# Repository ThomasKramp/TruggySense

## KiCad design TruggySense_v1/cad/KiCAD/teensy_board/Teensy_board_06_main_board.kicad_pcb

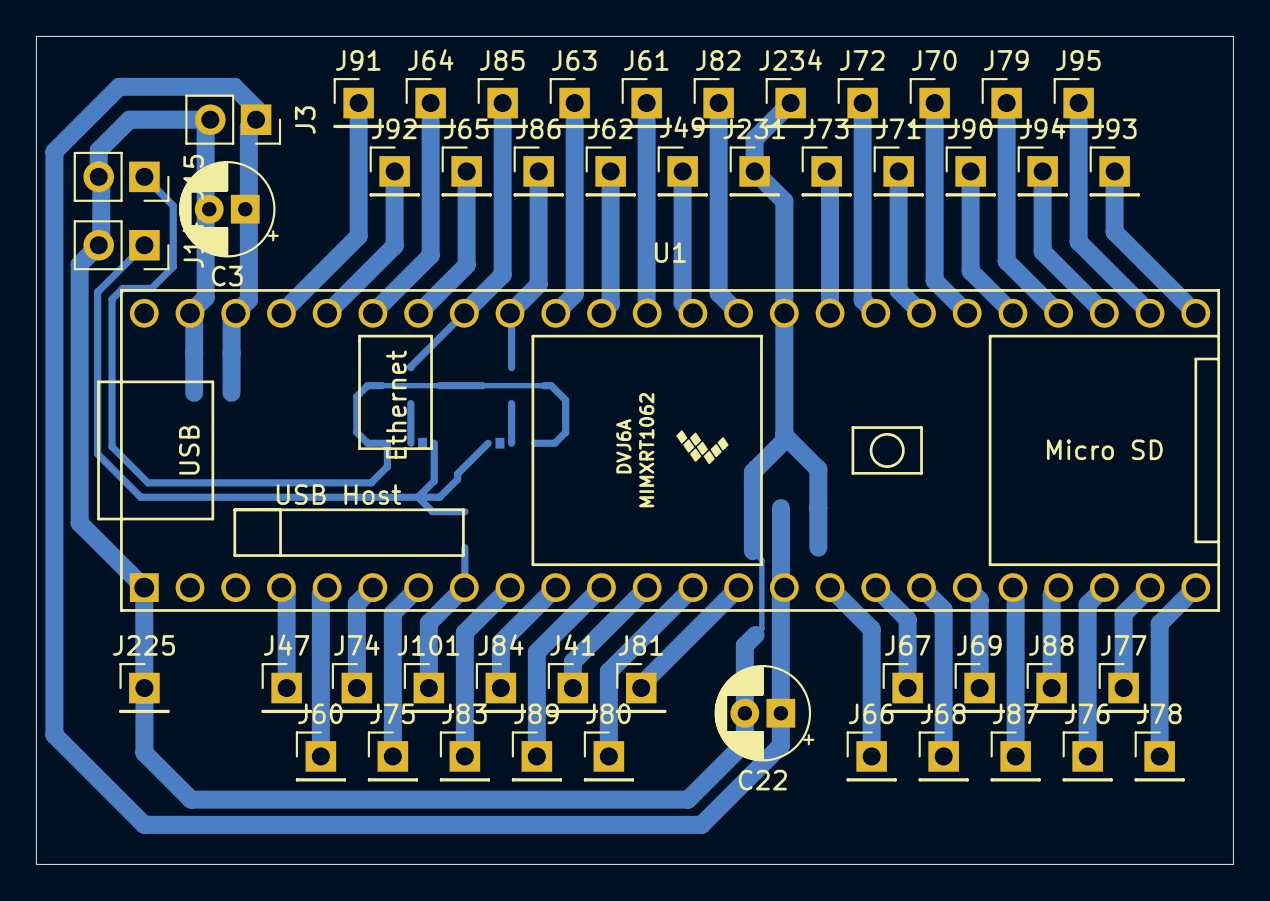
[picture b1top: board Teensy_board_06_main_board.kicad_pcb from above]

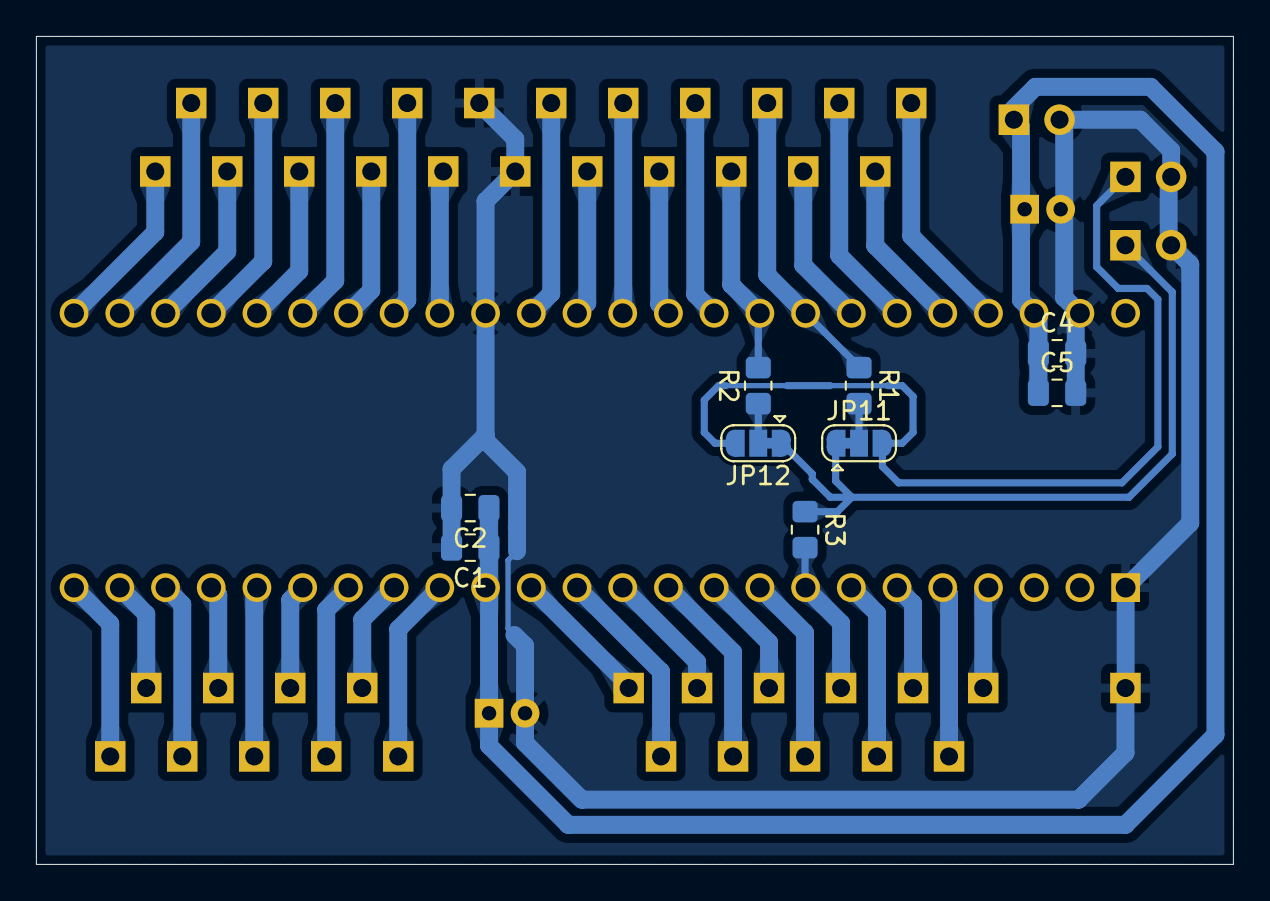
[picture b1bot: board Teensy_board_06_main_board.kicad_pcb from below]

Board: 2 copper layers, 66.5 x 46.0 mm, 58 parts (9 on the bottom side), 46 nets.

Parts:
C1, C4: 10µ; C_0805_2012Metric_Pad1.18x1.45mm_HandSolder
C2, C5: 10n; C_0805_2012Metric_Pad1.18x1.45mm_HandSolder
C3, C22: 100µ; CP_Radial_D5.0mm_P2.00mm
J3, J14, J15: Conn_01x02; PinSocket_1x02_P2.54mm_Vertical
J41, J47, J49, J60, J61, J62, J63, J64, J65, J66, J67, J68, J69, J70, J71, J72, J73, J74, J75, J76, J77, J78, J79, J80, J81, J82, J83, J84, J85, J86, J87, J88, J89, J90, J91, J92, J93, J94, J95, J101, J225, J231, J234: Conn_01x01; PinHeader_1x01_P2.54mm_Vertical
JP11, JP12: SolderJumper_3_Bridged12; SolderJumper-3_P1.3mm_Bridged12_RoundedPad1.0x1.5mm
R1, R2: 4k7; R_0805_2012Metric_Pad1.20x1.40mm_HandSolder
R3: 2k2; R_0805_2012Metric_Pad1.20x1.40mm_HandSolder
U1: Teensy4.1; Teensy41

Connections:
1_Wire: J101.1, R3.2, U1.8 (6_OUT1D)
+3.3V: J14.1, JP11.1 (A), JP12.1 (A), R3.1
+5V: J15.1, JP11.3 (B), JP12.3 (B)
ADC_I_JET: J72.1, U1.32 (40_A16)
ADC_I_M_FL: J68.1, U1.18 (26_A12_MOSI1)
ADC_I_M_FR: J67.1, U1.17 (25_A11_RX6_SDA2)
ADC_I_M_RL: J70.1, U1.30 (38_CS1_IN1)
ADC_I_M_RR: J69.1, U1.19 (27_A13_SCK1)
ADC_I_SERVO: J73.1, U1.33 (41_A17)
ADC_I_TEENSY: J71.1, U1.31 (39_MISO1_OUT1A)
ADC_V_B_C1: J49.1, U1.36 (14_A0_TX3_SPDIF_OUT)
ADC_V_B_C2: J61.1, U1.37 (15_A1_RX3_SPDIF_IN)
ADC_V_B_C3: J62.1, U1.38 (16_A2_RX4_SCL1)
ADC_V_B_C4: J63.1, U1.39 (17_A3_TX4_SDA1)
ADC_V_JET: J66.1, U1.16 (24_A10_TX6_SCL2)
ADC_V_MCU: J65.1, U1.42 (20_A6_TX5_LRCLK1)
ADC_V_PER: J64.1, U1.43 (21_A7_RX5_BCLK1)
EN_M_FL: J78.1, U1.24 (32_OUT1B)
EN_M_FR: J79.1, U1.28 (36_CS)
EN_M_RL: J76.1, U1.22 (30_CRX3)
EN_M_RR: J77.1, U1.23 (31_CTX3)
EN_W_FL: J74.1, U1.6 (4_BCLK2)
EN_W_FR: J75.1, U1.7 (5_IN2)
EN_W_RL: J47.1, U1.4 (2_OUT2)
EN_W_RR: J60.1, U1.5 (3_LRCLK2)
GND: C1.2, C2.2, C3.2, C4.2, C5.2, C22.2, J3.2, J14.2, J15.2, J225.1, J231.1, J234.1, U1.1 (GND), U1.34 (GND), U1.47 (GND)
GPS_RX: J84.1, U1.10 (8_TX2_IN1)
GPS_TX: J83.1, U1.9 (7_RX2_OUT1A)
I2C_SCL: J85.1, R1.1, U1.41 (19_A5_SCL)
I2C_SDA: J86.1, R2.2, U1.40 (18_A4_SDA)
IBUS_RX: J94.1, U1.27 (35_TX8)
IBUS_TX: J95.1, U1.26 (34_RX8)
LED_1: J87.1, U1.20 (28_RX7)
LED_2: J88.1, U1.21 (29_TX7)
unnamed: JP11.2 (C), R1.2
unnamed: JP12.2 (C), R2.1
PWM_ESC_M_FL: J91.1, U1.45 (23_A9_CRX1_MCLK1)
PWM_ESC_M_FR: J90.1, U1.29 (37_CS)
PWM_ESC_M_RL: J89.1, U1.11 (9_OUT1C)
PWM_ESC_M_RR: J92.1, U1.44 (22_A8_CTX1)
PWM_ESC_SERVO: J93.1, U1.25 (33_MCLK2)
SPI_CS: J41.1, U1.12 (10_CS_MQSR)
SPI_MISO: J81.1, U1.14 (12_MISO_MQSL)
SPI_MOSI: J80.1, U1.13 (11_MOSI_CTX1)
SPI_SCK: J82.1, U1.35 (13_SCK_LED)
VCC: C1.1, C2.1, C3.1, C4.1, C5.1, C22.1, J3.1, U1.15 (3V3), U1.46 (3V3)

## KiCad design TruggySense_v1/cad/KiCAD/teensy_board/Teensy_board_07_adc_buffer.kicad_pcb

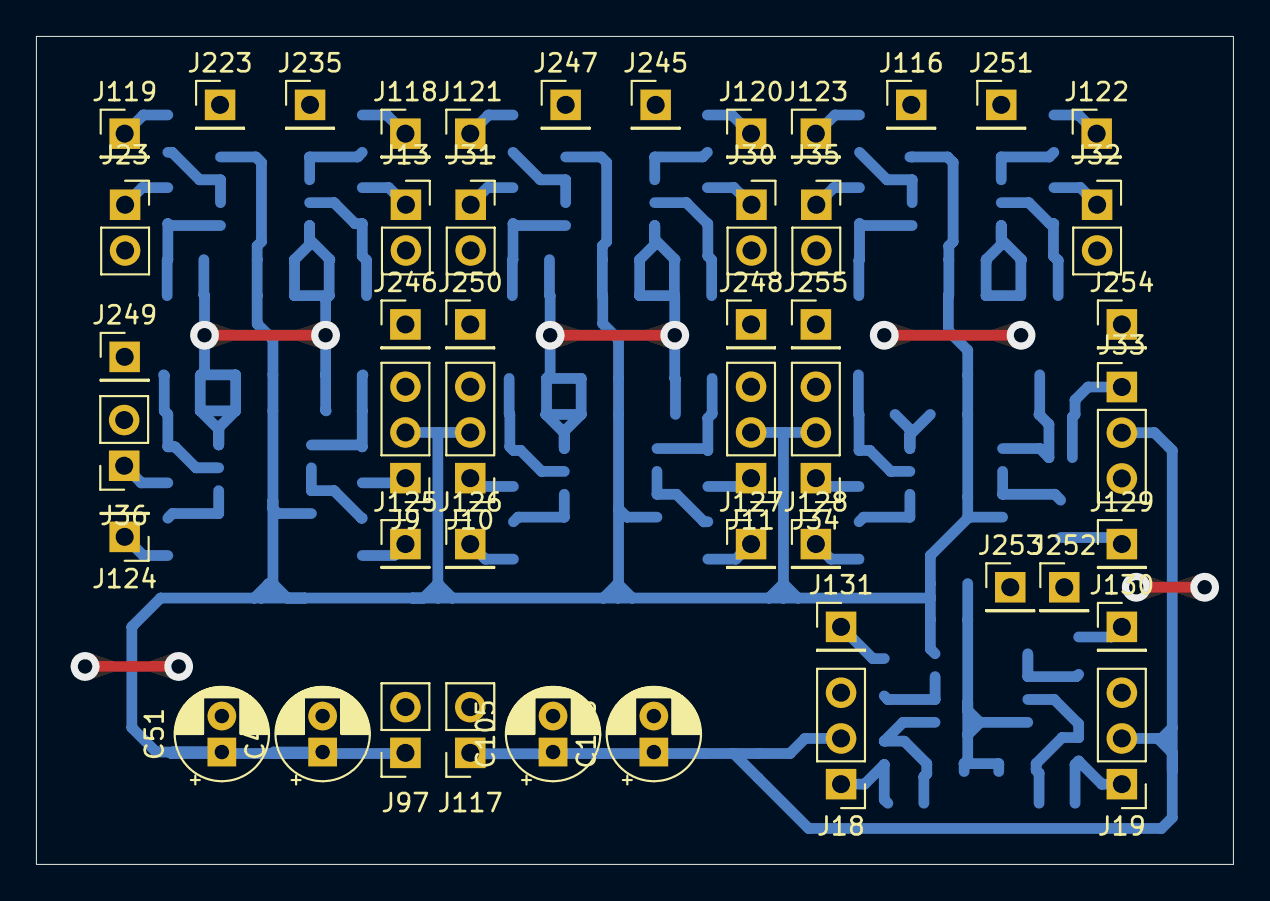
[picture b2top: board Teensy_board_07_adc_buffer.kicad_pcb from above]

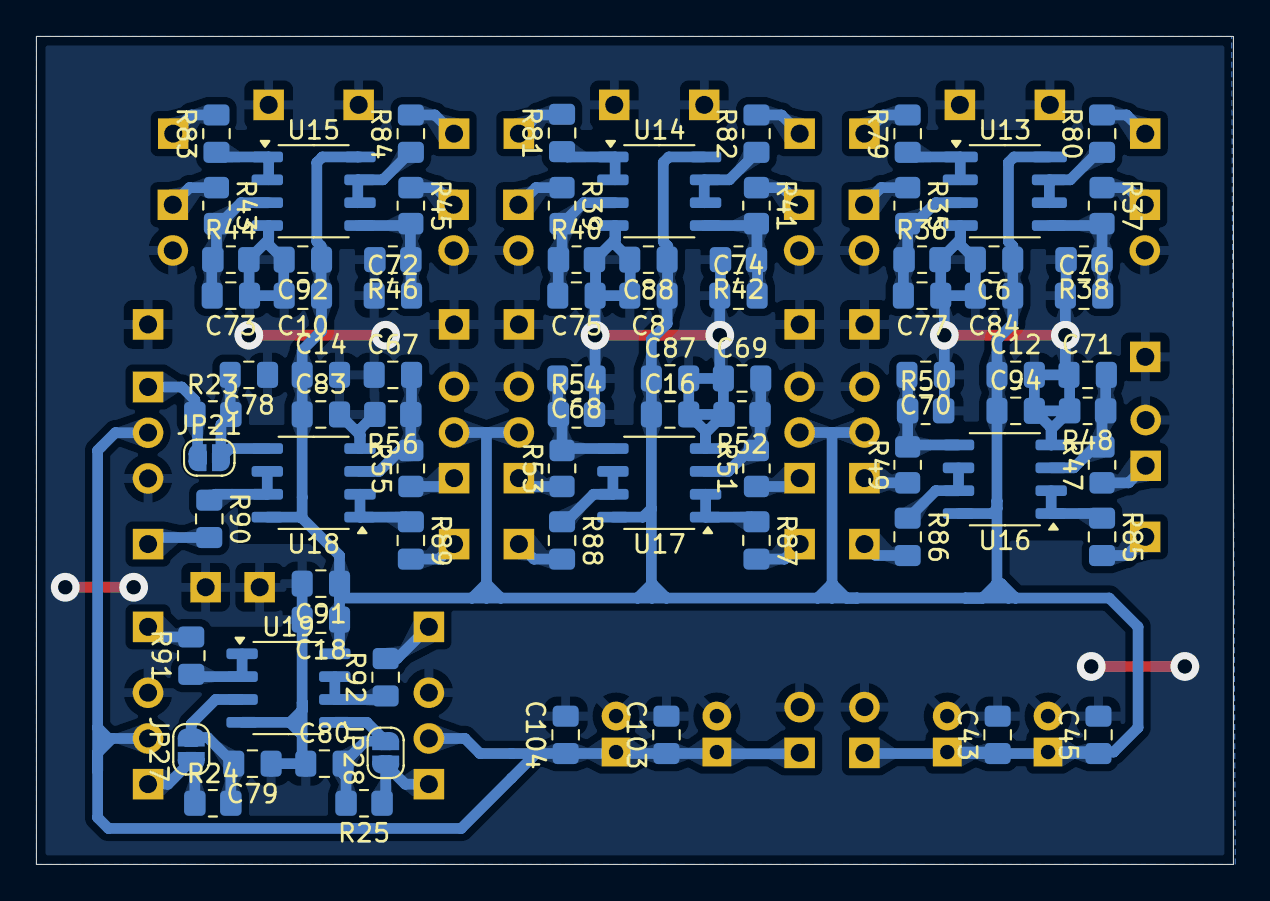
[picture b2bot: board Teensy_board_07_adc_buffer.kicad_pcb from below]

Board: 2 copper layers, 66.5 x 46.0 mm, 129 parts (81 on the bottom side), 24 nets.

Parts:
C6, C8, C10, C12, C14, C16, C18: 10u; C_0805_2012Metric_Pad1.18x1.45mm_HandSolder
C43, C45, C103: 10µ; C_0805_2012Metric_Pad1.18x1.45mm_HandSolder
C49, C51, C105, C106: 100µ; CP_Radial_D5.0mm_P2.00mm
C67, C68, C69, C70, C71, C72, C73, C74, C75, C76, C77, C78, C79, C80: 1µ; C_0805_2012Metric_Pad1.18x1.45mm_HandSolder
C83, C84, C87, C88, C91, C92, C94, C104: 10n; C_0805_2012Metric_Pad1.18x1.45mm_HandSolder
J9: CUR_M_FR; PinHeader_1x03_P2.54mm_Vertical
J10: CUR_M_FL; PinHeader_1x03_P2.54mm_Vertical
J11: CUR_M_RR; PinHeader_1x03_P2.54mm_Vertical
J13: V_BATT_C1; PinSocket_1x02_P2.54mm_Vertical
J18: CUR_SERVO; PinHeader_1x03_P2.54mm_Vertical
J19: CUR_JETSON; PinHeader_1x03_P2.54mm_Vertical
J23: V_BATT_C2; PinSocket_1x02_P2.54mm_Vertical
J30: V_BATT_C3; PinSocket_1x02_P2.54mm_Vertical
J31: V_BATT_C4; PinSocket_1x02_P2.54mm_Vertical
J32: VCC_PER_3V3; PinSocket_1x02_P2.54mm_Vertical
J33: CUR_TEENSY; PinHeader_1x03_P2.54mm_Vertical
J34: CUR_M_RL; PinHeader_1x03_P2.54mm_Vertical
J35: VCC_MCU_3V3; PinSocket_1x02_P2.54mm_Vertical
J36: VCC_JET_5V; PinSocket_1x02_P2.54mm_Vertical
J97, J117: Conn_01x02; PinSocket_1x02_P2.54mm_Vertical
J116, J118, J119, J120, J121, J122, J123, J124, J125, J126, J127, J128, J129, J130, J131, J223, J235, J245, J246, J247, J248, J249, J250, J251, J252, J253, J254, J255: Conn_01x01; PinHeader_1x01_P2.54mm_Vertical
JP21, JP27, JP28: SolderJumper_2_Open; SolderJumper-2_P1.3mm_Open_RoundedPad1.0x1.5mm
R23, R24, R25, R35, R37, R39, R41, R43, R45, R47, R49, R51, R53, R55: 10k; R_0805_2012Metric_Pad1.20x1.40mm_HandSolder
R36, R38, R40, R42: 33k; R_0805_2012Metric_Pad1.20x1.40mm_HandSolder
R44, R46: 82k; R_0805_2012Metric_Pad1.20x1.40mm_HandSolder
R48, R50, R52, R54, R56: 18k; R_0805_2012Metric_Pad1.20x1.40mm_HandSolder
R79, R80, R81, R82, R83, R84, R85, R86, R87, R88, R89, R90, R91, R92: 10; C_0805_2012Metric_Pad1.18x1.45mm_HandSolder
U13: OPA2890ID; SOIC-8_3.9x4.9mm_P1.27mm
U14, U15, U16, U17, U18, U19: OPA2890ID; SO-8_3.9x4.9mm_P1.27mm

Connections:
+3.3V: C103.1, C104.1, C105.1, C106.1, J18.2, J19.2, J33.2, J117.1
+5V: C6.1, C8.1, C10.1, C12.1, C14.1, C16.1, C18.1, C43.1, C45.1, C49.1, C51.1, C83.1, C84.1, C87.1, C88.1, C91.1, C92.1, C94.1, J9.2, J10.2, J11.2, J34.2, J97.1, U13.8 (V+), U14.8 (V+), U15.8 (V+), U16.8 (V+), U17.8 (V+), U18.8 (V+), U19.8 (V+)
/ADC inputs/Buffer/IN_8: C70.2, R49.2, R50.1, U16.5 (+)
/ADC inputs/Buffer/IN_9: C69.2, R51.2, R52.1, U17.3 (+)
/ADC inputs/Buffer/IN_10: C68.2, R53.2, R54.1, U17.5 (+)
/ADC inputs/Buffer/IN_11: C67.2, R55.2, R56.1, U18.3 (+)
/ADC inputs/Buffer/IN_12: C78.2, JP21.2 (B), R23.2, U18.5 (+)
/ADC inputs/Buffer/IN_13: C79.2, JP27.2 (B), R24.2, U19.3 (+)
/ADC inputs/Buffer/IN_14: C80.2, JP28.2 (B), R25.2, U19.5 (+)
/ADC inputs/Buffer/OUT_8: J125.1, R86.2
/ADC inputs/Buffer/OUT_9: J126.1, R87.2
/ADC inputs/Buffer/OUT_10: J127.1, R88.2
/ADC inputs/Buffer/OUT_11: J128.1, R89.2
/ADC inputs/Buffer/OUT_12: J129.1, R90.2
/ADC inputs/Buffer/OUT_13: J130.1, R91.2
/ADC inputs/Buffer/OUT_14: J131.1, R92.2
GND: C6.2, C8.2, C10.2, C12.2, C14.2, C16.2, C18.2, C43.2, C45.2, C49.2, C51.2, C67.1, C68.1, C69.1, C70.1, C71.1, C72.1, C73.1, C74.1, C75.1, C76.1, C77.1, C78.1, C79.1, C80.1, C83.2, C84.2, C87.2, C88.2, C91.2, C92.2, C94.2, C103.2, C104.2, C105.2, C106.2, J9.3, J10.3, J11.3, J13.2, J18.3, J19.3, J23.2, J30.2, J31.2, J32.2, J33.3, J34.3, J35.2, J36.2, J97.2, J116.1, J117.2, J223.1, J235.1, J245.1, J246.1, J247.1, J248.1, J249.1, J250.1, J251.1, J252.1, J253.1, J254.1, J255.1, R36.2, R38.2, R40.2, R42.2, R44.2, R46.2, R48.2, R50.2, R52.2, R54.2, R56.2, U13.4 (V-), U14.4 (V-), U15.4 (V-), U16.4 (V-), U17.4 (V-), U18.4 (V-), U19.4 (V-)
unnamed: J9.1, R49.1
unnamed: J10.1, R51.1
unnamed: J11.1, R53.1
unnamed: J18.1, JP28.1 (A), R25.1
unnamed: J19.1, JP27.1 (A), R24.1
unnamed: J33.1, JP21.1 (A), R23.1
unnamed: J34.1, R55.1

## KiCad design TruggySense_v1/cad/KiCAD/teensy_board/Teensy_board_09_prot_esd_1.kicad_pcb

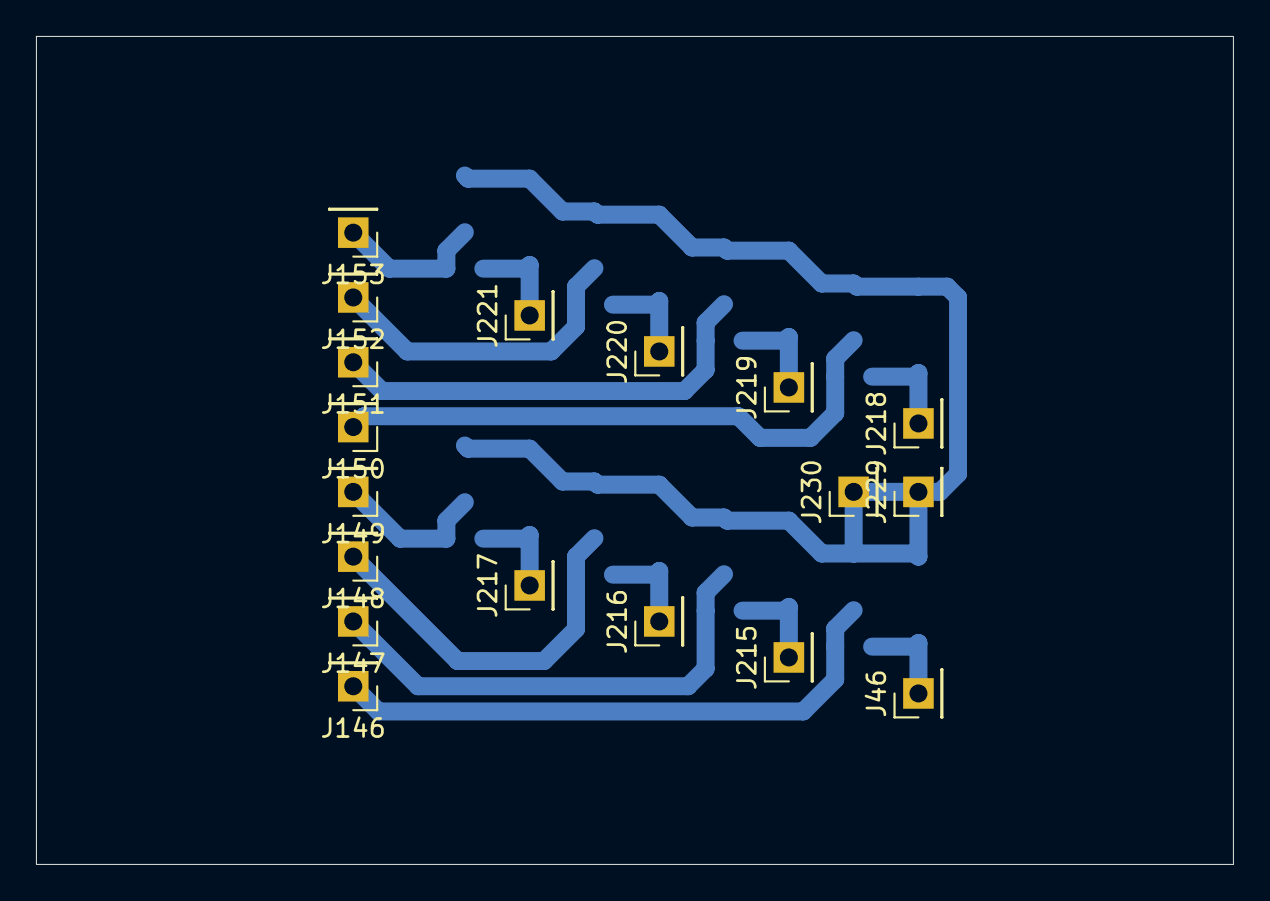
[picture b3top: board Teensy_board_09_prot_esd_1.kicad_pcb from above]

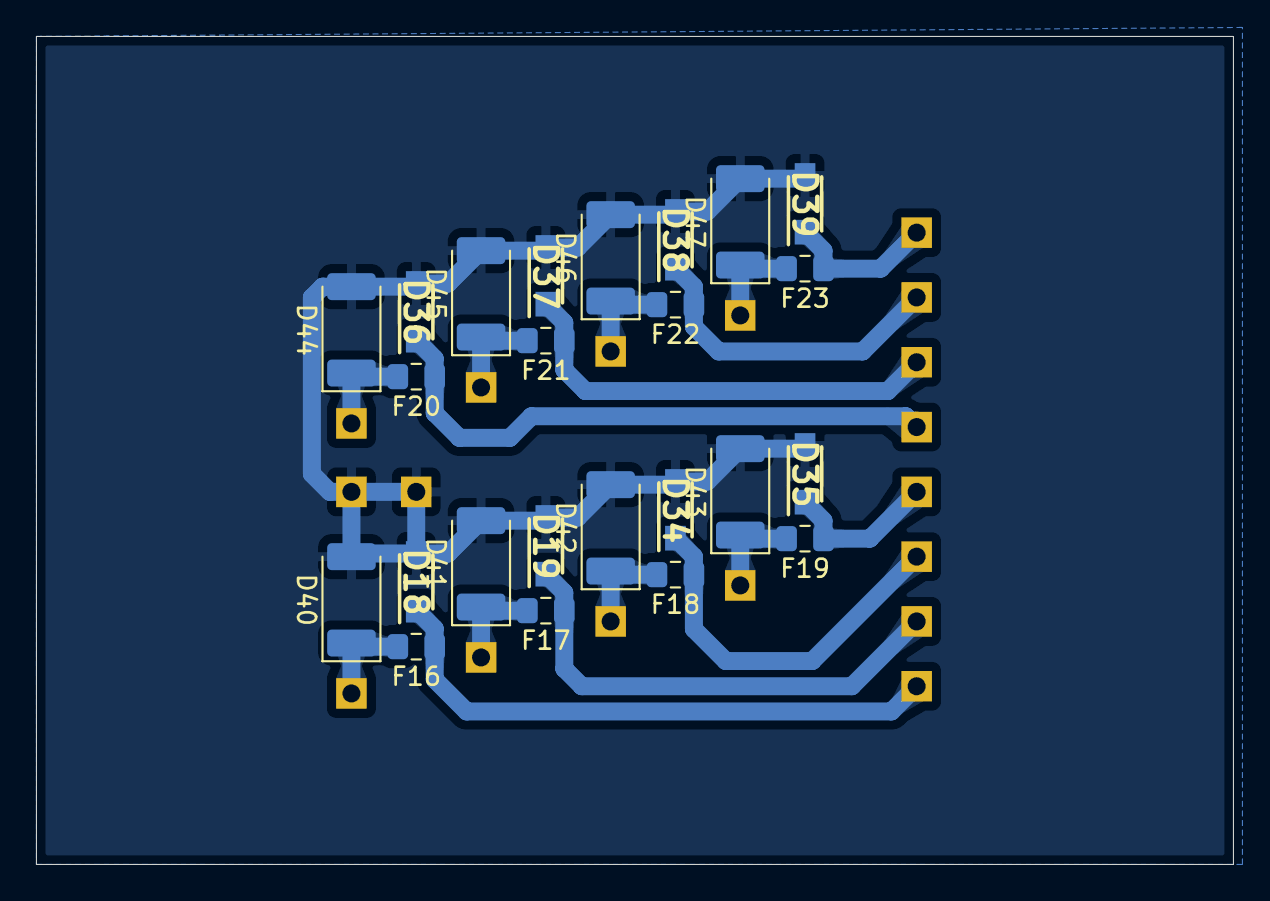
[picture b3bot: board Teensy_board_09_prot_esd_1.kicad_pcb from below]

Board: 2 copper layers, 66.5 x 46.0 mm, 42 parts (24 on the bottom side), 17 nets.

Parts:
D18, D19, D34, D35, D36, D37, D38, D39: TVS_SMF3.3; SOD3718X108N
D40, D41, D42, D43, D44, D45, D46, D47: Zener_ZM4729A-GS18; D_MELF
F16, F17, F18, F19, F20, F21, F22, F23: SMD0805B010TF; Fuse_0805_2012Metric_Pad1.15x1.40mm_HandSolder
J46, J146, J147, J148, J149, J150, J151, J152, J153, J215, J216, J217, J218, J219, J220, J221, J229, J230: Conn_01x01; PinHeader_1x01_P2.54mm_Vertical

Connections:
/Encoder/Protection_IO/IN_1: D18.1 (K), F16.1, J146.1
/Encoder/Protection_IO/IN_2: D19.1 (K), F17.1, J147.1
/Encoder/Protection_IO/IN_3: D34.1 (K), F18.1, J148.1
/Encoder/Protection_IO/IN_4: D35.1 (K), F19.1, J149.1
/Encoder/Protection_IO/IN_5: D36.1 (K), F20.1, J150.1
/Encoder/Protection_IO/IN_6: D37.1 (K), F21.1, J151.1
/Encoder/Protection_IO/IN_7: D38.1 (K), F22.1, J152.1
/Encoder/Protection_IO/IN_8: D39.1 (K), F23.1, J153.1
/Encoder/Protection_IO/OUT_1: D40.1 (K), F16.2, J46.1
/Encoder/Protection_IO/OUT_2: D41.1 (K), F17.2, J215.1
/Encoder/Protection_IO/OUT_3: D42.1 (K), F18.2, J216.1
/Encoder/Protection_IO/OUT_4: D43.1 (K), F19.2, J217.1
/Encoder/Protection_IO/OUT_5: D44.1 (K), F20.2, J218.1
/Encoder/Protection_IO/OUT_6: D45.1 (K), F21.2, J219.1
/Encoder/Protection_IO/OUT_7: D46.1 (K), F22.2, J220.1
/Encoder/Protection_IO/OUT_8: D47.1 (K), F23.2, J221.1
GND: D18.2 (A), D19.2 (A), D34.2 (A), D35.2 (A), D36.2 (A), D37.2 (A), D38.2 (A), D39.2 (A), D40.2 (A), D41.2 (A), D42.2 (A), D43.2 (A), D44.2 (A), D45.2 (A), D46.2 (A), D47.2 (A), J229.1, J230.1

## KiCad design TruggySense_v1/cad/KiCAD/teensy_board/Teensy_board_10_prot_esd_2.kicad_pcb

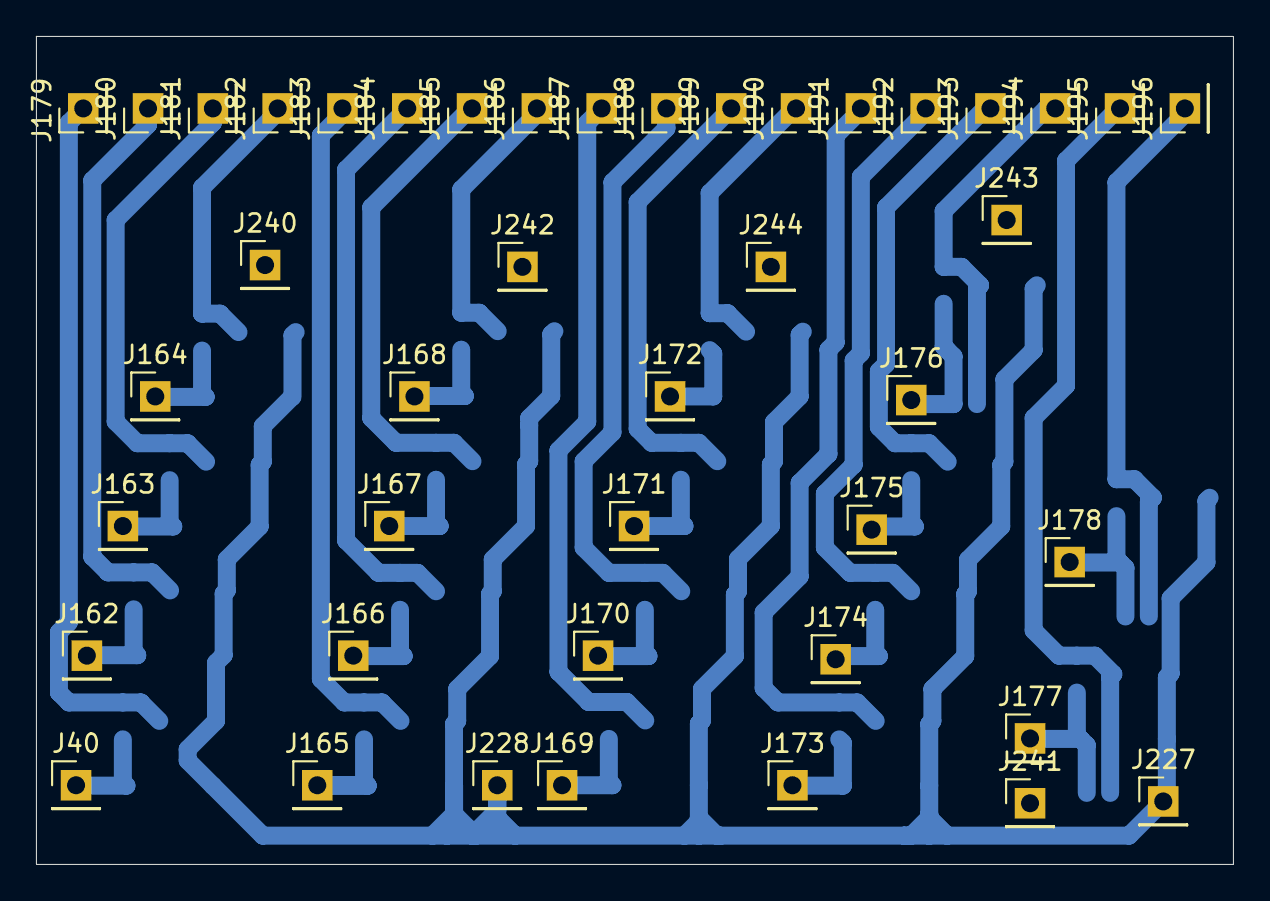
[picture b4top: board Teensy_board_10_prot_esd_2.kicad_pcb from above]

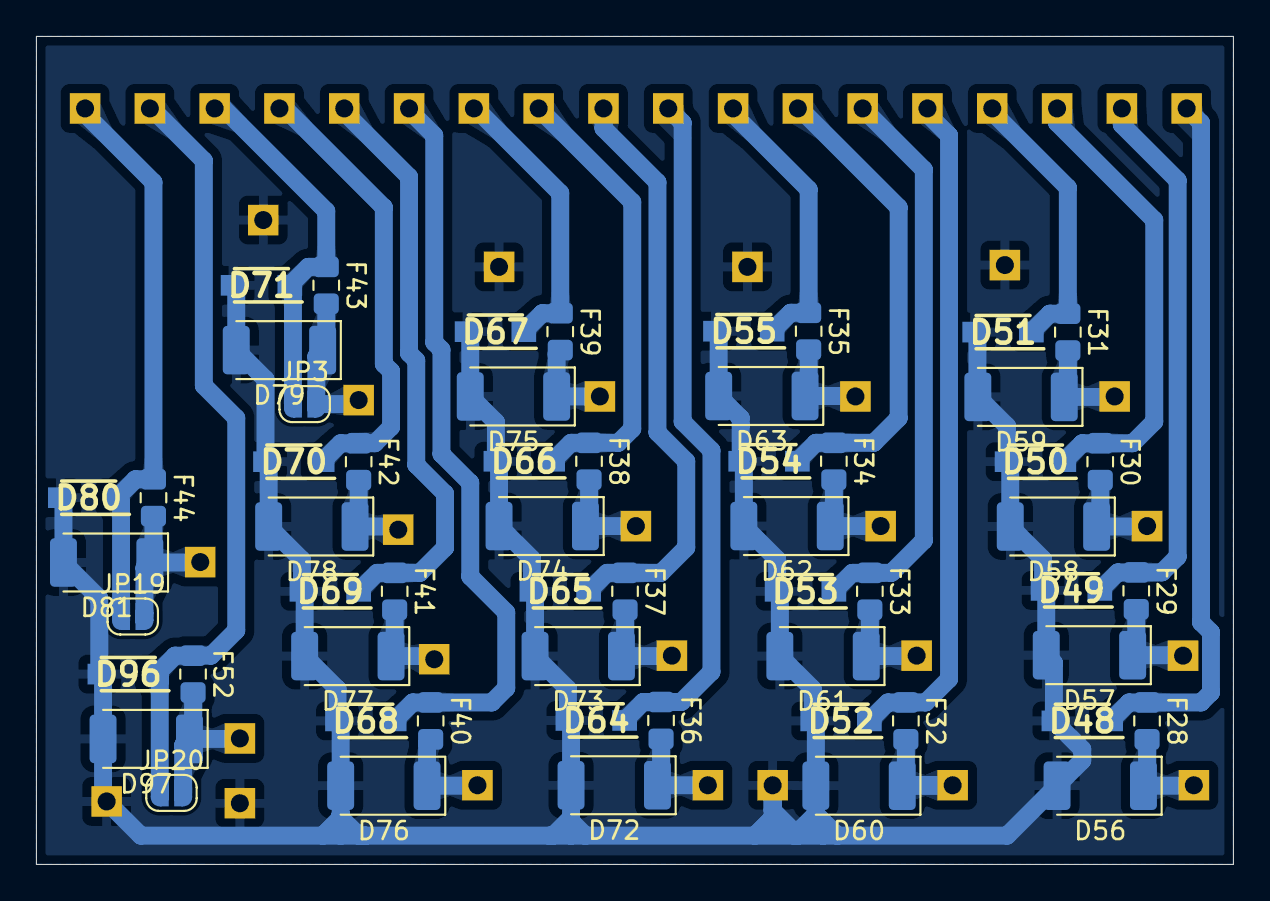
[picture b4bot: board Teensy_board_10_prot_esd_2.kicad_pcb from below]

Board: 2 copper layers, 66.5 x 46.0 mm, 100 parts (57 on the bottom side), 37 nets.

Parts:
D48, D49, D50, D51, D52, D53, D54, D55, D64, D65, D66, D67, D68, D69, D70, D71, D80, D96: TVS_SMF3.3; SOD3718X108N
D56, D57, D58, D59, D60, D61, D62, D63, D72, D73, D74, D75, D76, D77, D78, D79, D81, D97: Zener_ZM4729A-GS18; D_MELF
F28, F29, F30, F31, F32, F33, F34, F35, F36, F37, F38, F39, F40, F41, F42, F43, F44, F52: SMD0805B010TF; Fuse_0805_2012Metric_Pad1.15x1.40mm_HandSolder
J40, J162, J163, J164, J165, J166, J167, J168, J169, J170, J171, J172, J173, J174, J175, J176, J177, J178, J179, J180, J181, J182, J183, J184, J185, J186, J187, J188, J189, J190, J191, J192, J193, J194, J195, J196, J227, J228, J240, J241, J242, J243, J244: Conn_01x01; PinHeader_1x01_P2.54mm_Vertical
JP3, JP19, JP20: SolderJumper_2_Open; SolderJumper-2_P1.3mm_Open_RoundedPad1.0x1.5mm

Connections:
/Communication & pheripherals/Protection_IO1/IN_1: D48.1 (K), F28.1, J179.1
/Communication & pheripherals/Protection_IO1/IN_2: D49.1 (K), F29.1, J180.1
/Communication & pheripherals/Protection_IO1/IN_3: D50.1 (K), F30.1, J181.1
/Communication & pheripherals/Protection_IO1/IN_4: D51.1 (K), F31.1, J182.1
/Communication & pheripherals/Protection_IO1/IN_5: D52.1 (K), F32.1, J183.1
/Communication & pheripherals/Protection_IO1/IN_6: D53.1 (K), F33.1, J184.1
/Communication & pheripherals/Protection_IO1/IN_7: D54.1 (K), F34.1, J185.1
/Communication & pheripherals/Protection_IO1/IN_8: D55.1 (K), F35.1, J186.1
/Communication & pheripherals/Protection_IO1/IN_9: D64.1 (K), F36.1, J187.1
/Communication & pheripherals/Protection_IO1/IN_10: D65.1 (K), F37.1, J188.1
/Communication & pheripherals/Protection_IO1/IN_11: D66.1 (K), F38.1, J189.1
/Communication & pheripherals/Protection_IO1/IN_12: D67.1 (K), F39.1, J190.1
/Communication & pheripherals/Protection_IO1/IN_13: D68.1 (K), F40.1, J191.1
/Communication & pheripherals/Protection_IO1/IN_14: D69.1 (K), F41.1, J192.1
/Communication & pheripherals/Protection_IO1/IN_15: D70.1 (K), F42.1, J193.1
/Communication & pheripherals/Protection_IO1/IN_16: D71.1 (K), F43.1, J194.1, JP3.1 (A)
/Communication & pheripherals/Protection_IO1/IN_17: D96.1 (K), F52.1, J195.1, JP20.1 (A)
/Communication & pheripherals/Protection_IO1/IN_18: D80.1 (K), F44.1, J196.1, JP19.1 (A)
/Communication & pheripherals/Protection_IO1/OUT_1: D56.1 (K), F28.2, J40.1
/Communication & pheripherals/Protection_IO1/OUT_2: D57.1 (K), F29.2, J162.1
/Communication & pheripherals/Protection_IO1/OUT_3: D58.1 (K), F30.2, J163.1
/Communication & pheripherals/Protection_IO1/OUT_4: D59.1 (K), F31.2, J164.1
/Communication & pheripherals/Protection_IO1/OUT_5: D60.1 (K), F32.2, J165.1
/Communication & pheripherals/Protection_IO1/OUT_6: D61.1 (K), F33.2, J166.1
/Communication & pheripherals/Protection_IO1/OUT_7: D62.1 (K), F34.2, J167.1
/Communication & pheripherals/Protection_IO1/OUT_8: D63.1 (K), F35.2, J168.1
/Communication & pheripherals/Protection_IO1/OUT_9: D72.1 (K), F36.2, J169.1
/Communication & pheripherals/Protection_IO1/OUT_10: D73.1 (K), F37.2, J170.1
/Communication & pheripherals/Protection_IO1/OUT_11: D74.1 (K), F38.2, J171.1
/Communication & pheripherals/Protection_IO1/OUT_12: D75.1 (K), F39.2, J172.1
/Communication & pheripherals/Protection_IO1/OUT_13: D76.1 (K), F40.2, J173.1
/Communication & pheripherals/Protection_IO1/OUT_14: D77.1 (K), F41.2, J174.1
/Communication & pheripherals/Protection_IO1/OUT_15: D78.1 (K), F42.2, J175.1
/Communication & pheripherals/Protection_IO1/OUT_16: D79.1 (K), F43.2, J176.1, JP3.2 (B)
/Communication & pheripherals/Protection_IO1/OUT_17: D97.1 (K), F52.2, J177.1, JP20.2 (B)
/Communication & pheripherals/Protection_IO1/OUT_18: D81.1 (K), F44.2, J178.1, JP19.2 (B)
GND: D48.2 (A), D49.2 (A), D50.2 (A), D51.2 (A), D52.2 (A), D53.2 (A), D54.2 (A), D55.2 (A), D56.2 (A), D57.2 (A), D58.2 (A), D59.2 (A), D60.2 (A), D61.2 (A), D62.2 (A), D63.2 (A), D64.2 (A), D65.2 (A), D66.2 (A), D67.2 (A), D68.2 (A), D69.2 (A), D70.2 (A), D71.2 (A), D72.2 (A), D73.2 (A), D74.2 (A), D75.2 (A), D76.2 (A), D77.2 (A), D78.2 (A), D79.2 (A), D80.2 (A), D81.2 (A), D96.2 (A), D97.2 (A), J227.1, J228.1, J240.1, J241.1, J242.1, J243.1, J244.1

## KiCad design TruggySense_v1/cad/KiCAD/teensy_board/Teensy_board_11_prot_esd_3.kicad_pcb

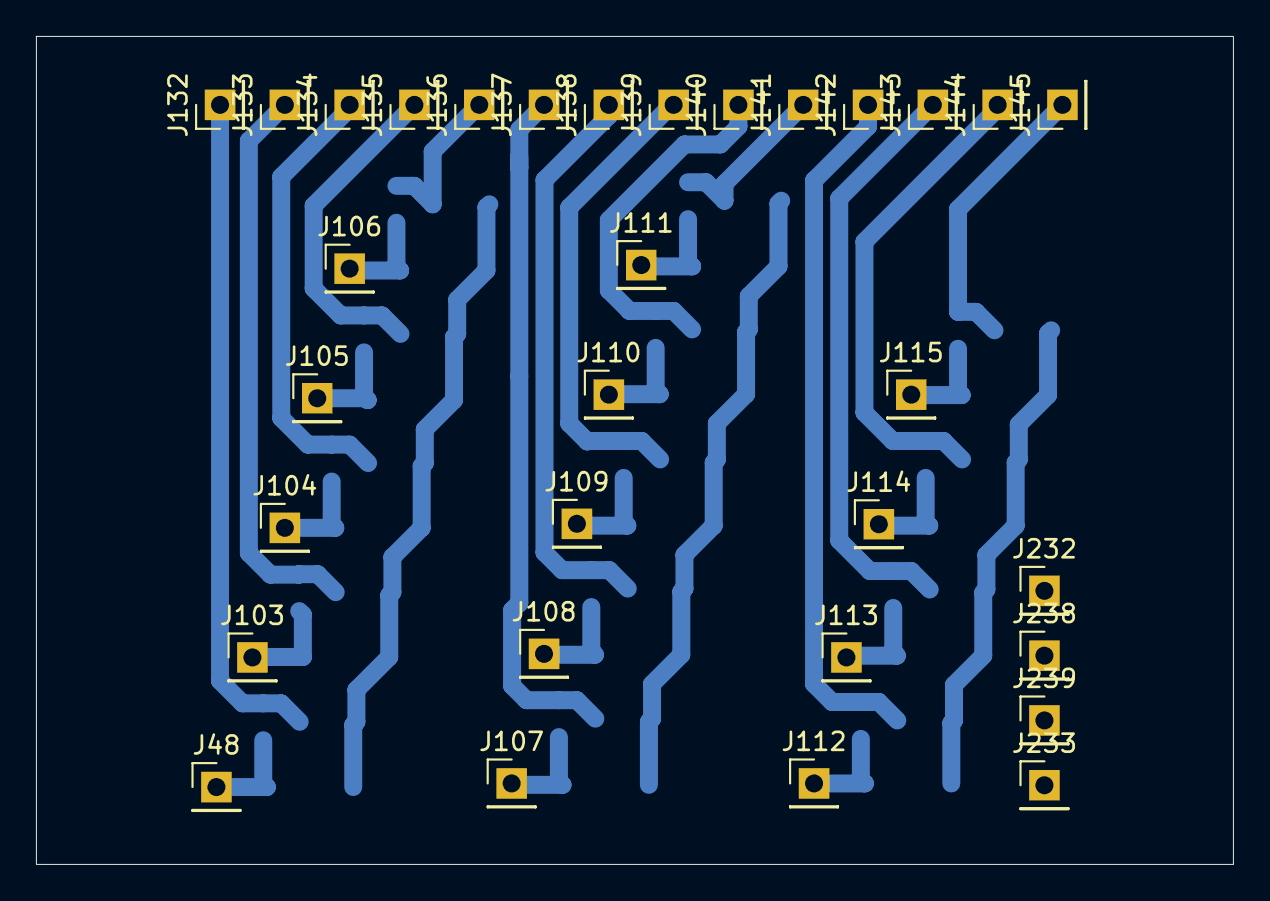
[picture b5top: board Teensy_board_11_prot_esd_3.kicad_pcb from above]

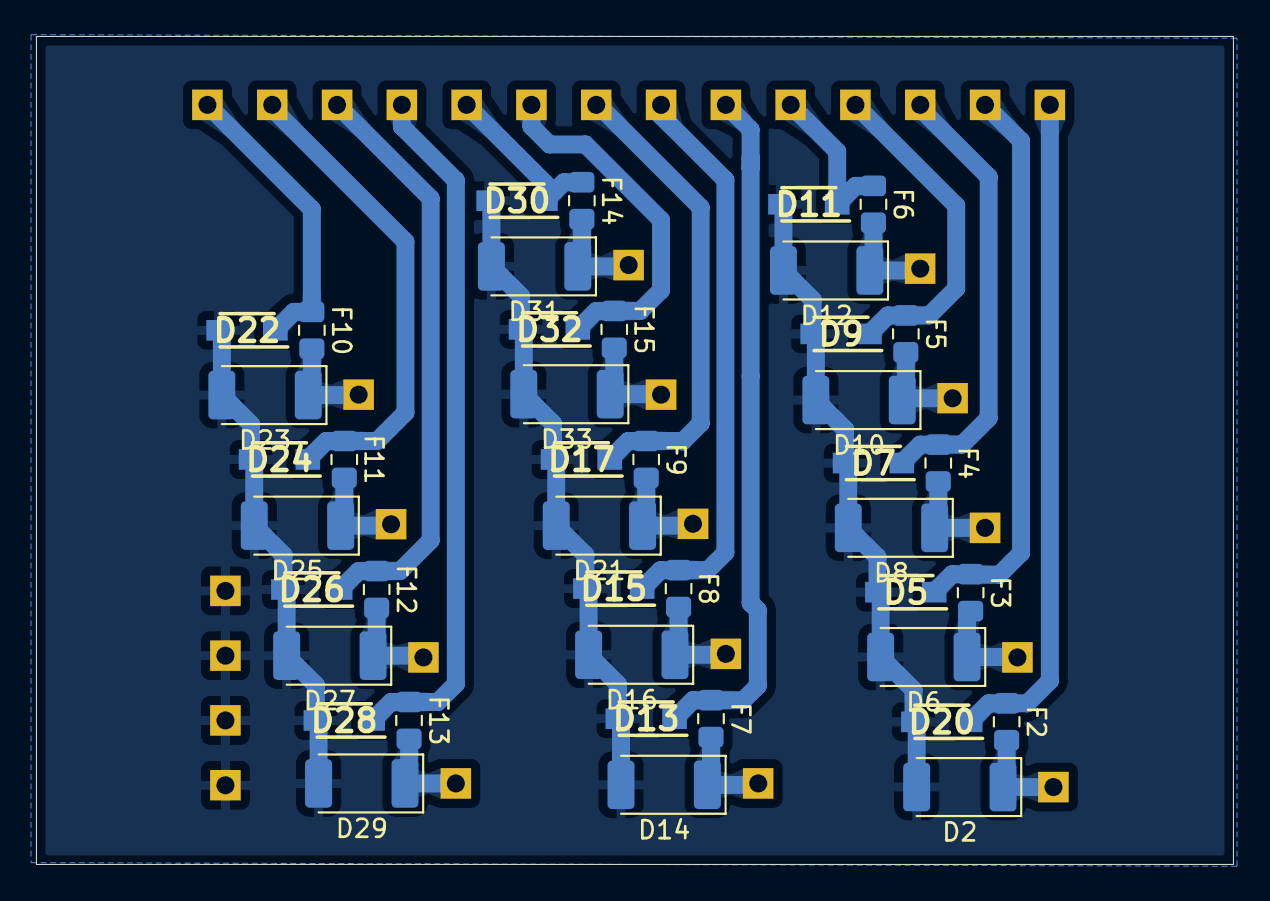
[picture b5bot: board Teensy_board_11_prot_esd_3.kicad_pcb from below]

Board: 2 copper layers, 66.5 x 46.0 mm, 74 parts (42 on the bottom side), 29 nets.

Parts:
D2, D6, D8, D10, D12, D14, D16, D21, D23, D25, D27, D29, D31, D33: Zener_ZM4729A-GS18; D_MELF
D5, D7, D9, D11, D13, D15, D17, D20, D22, D24, D26, D28, D30, D32: TVS_SMF3.3; SOD3718X108N
F2, F3, F4, F5, F6, F7, F8, F9, F10, F11, F12, F13, F14, F15: SMD0805B010TF; Fuse_0805_2012Metric_Pad1.15x1.40mm_HandSolder
J48, J103, J104, J105, J106, J107, J108, J109, J110, J111, J112, J113, J114, J115, J132, J133, J134, J135, J136, J137, J138, J139, J140, J141, J142, J143, J144, J145, J232, J233, J238, J239: Conn_01x01; PinHeader_1x01_P2.54mm_Vertical

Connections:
/ADC inputs/Protection_circuit_ADC1/IN_1: D20.1 (K), F2.1, J132.1
/ADC inputs/Protection_circuit_ADC1/IN_2: D5.1 (K), F3.1, J133.1
/ADC inputs/Protection_circuit_ADC1/IN_3: D7.1 (K), F4.1, J134.1
/ADC inputs/Protection_circuit_ADC1/IN_4: D9.1 (K), F5.1, J135.1
/ADC inputs/Protection_circuit_ADC1/IN_5: D11.1 (K), F6.1, J136.1
/ADC inputs/Protection_circuit_ADC1/IN_6: D13.1 (K), F7.1, J137.1
/ADC inputs/Protection_circuit_ADC1/IN_7: D15.1 (K), F8.1, J138.1
/ADC inputs/Protection_circuit_ADC1/IN_8: D17.1 (K), F9.1, J139.1
/ADC inputs/Protection_circuit_ADC1/IN_9: D32.1 (K), F15.1, J140.1
/ADC inputs/Protection_circuit_ADC1/IN_10: D30.1 (K), F14.1, J141.1
/ADC inputs/Protection_circuit_ADC1/IN_11: D28.1 (K), F13.1, J142.1
/ADC inputs/Protection_circuit_ADC1/IN_12: D26.1 (K), F12.1, J143.1
/ADC inputs/Protection_circuit_ADC1/IN_13: D24.1 (K), F11.1, J144.1
/ADC inputs/Protection_circuit_ADC1/IN_14: D22.1 (K), F10.1, J145.1
/ADC inputs/Protection_circuit_ADC1/OUT_1: D2.1 (K), F2.2, J48.1
/ADC inputs/Protection_circuit_ADC1/OUT_2: D6.1 (K), F3.2, J103.1
/ADC inputs/Protection_circuit_ADC1/OUT_3: D8.1 (K), F4.2, J104.1
/ADC inputs/Protection_circuit_ADC1/OUT_4: D10.1 (K), F5.2, J105.1
/ADC inputs/Protection_circuit_ADC1/OUT_5: D12.1 (K), F6.2, J106.1
/ADC inputs/Protection_circuit_ADC1/OUT_6: D14.1 (K), F7.2, J107.1
/ADC inputs/Protection_circuit_ADC1/OUT_7: D16.1 (K), F8.2, J108.1
/ADC inputs/Protection_circuit_ADC1/OUT_8: D21.1 (K), F9.2, J109.1
/ADC inputs/Protection_circuit_ADC1/OUT_9: D33.1 (K), F15.2, J110.1
/ADC inputs/Protection_circuit_ADC1/OUT_10: D31.1 (K), F14.2, J111.1
/ADC inputs/Protection_circuit_ADC1/OUT_11: D29.1 (K), F13.2, J112.1
/ADC inputs/Protection_circuit_ADC1/OUT_12: D27.1 (K), F12.2, J113.1
/ADC inputs/Protection_circuit_ADC1/OUT_13: D25.1 (K), F11.2, J114.1
/ADC inputs/Protection_circuit_ADC1/OUT_14: D23.1 (K), F10.2, J115.1
GND: D2.2 (A), D5.2 (A), D6.2 (A), D7.2 (A), D8.2 (A), D9.2 (A), D10.2 (A), D11.2 (A), D12.2 (A), D13.2 (A), D14.2 (A), D15.2 (A), D16.2 (A), D17.2 (A), D20.2 (A), D21.2 (A), D22.2 (A), D23.2 (A), D24.2 (A), D25.2 (A), D26.2 (A), D27.2 (A), D28.2 (A), D29.2 (A), D30.2 (A), D31.2 (A), D32.2 (A), D33.2 (A), J232.1, J233.1, J238.1, J239.1

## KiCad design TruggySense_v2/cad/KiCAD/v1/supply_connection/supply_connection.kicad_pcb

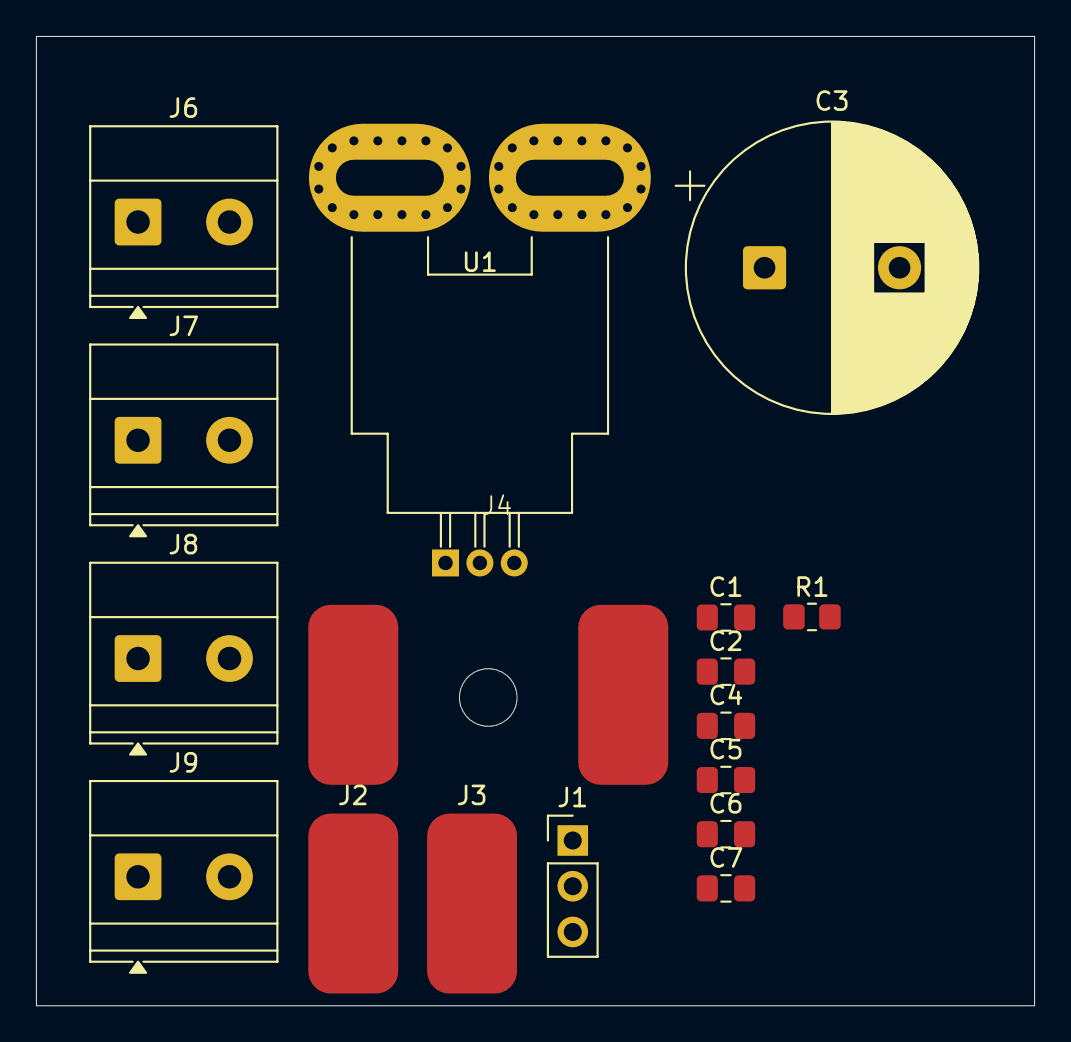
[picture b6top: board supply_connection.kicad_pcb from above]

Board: 2 copper layers, 55.4 x 53.8 mm, 17 parts (0 on the bottom side), 11 nets, no tracks yet.

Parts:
C1: 1µ; C_0805_2012Metric_Pad1.18x1.45mm_HandSolder
C2: 100n; C_0805_2012Metric_Pad1.18x1.45mm_HandSolder
C3: 1000µ; CP_Radial_D16.0mm_P7.50mm
C4, C5, C6, C7: 10µ; C_0805_2012Metric_Pad1.18x1.45mm_HandSolder
J1: Supply_I_Sens; PinHeader_1x03_P2.54mm_Vertical
J2: ESC-; SolderWirePad_1x01_SMD_5x10mm
J3: ESC+; SolderWirePad_1x01_SMD_5x10mm
J4: BAT; EC5_cable_pads
J6: JET_5V; TerminalBlock_Phoenix_MKDS-1,5-2-5.08_1x02_P5.08mm_Horizont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
J7: TEENSY_3V3; TerminalBlock_Phoenix_MKDS-1,5-2-5.08_1x02_P5.08mm_Horizont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
J8: PHERI_3V3; TerminalBlock_Phoenix_MKDS-1,5-2-5.08_1x02_P5.08mm_Horizont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
J9: PHERI_5V; TerminalBlock_Phoenix_MKDS-1,5-2-5.08_1x02_P5.08mm_Horizont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
R1: 8k2; R_0805_2012Metric_Pad1.20x1.40mm_HandSolder
U1: ACS758xCB-200B-PFF; Allegro_CB_PFF

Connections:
+3.3V: C2.2, J1.2, U1.1 (VCC)
GND: C3.2, C4.2, C5.2, C6.2, C7.2, J2.1, J4.2 (V-), J6.1, J7.1, J8.1, J9.1
GND2: C1.1, C2.1, J1.3, U1.2 (GND)
unnamed: C7.1, J6.2
unnamed: C6.1, J9.2
unnamed: C5.1, J7.2
unnamed: C4.1, J8.2
unnamed: C1.2, J1.1, R1.2
unnamed: J3.1, U1.5 (IP-)
unnamed: R1.1, U1.3 (VIOUT)
VCC: C3.1, J4.1 (V+), U1.4 (IP+)
